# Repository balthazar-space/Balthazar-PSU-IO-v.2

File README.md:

# Balthazar

Open-hardware laptop computer modules description and concept.

These are electronic schematic modules as presented at https://balthazar.space/wiki/Balthazar with the main aim for team access. See the [main repository](https://github.com/balthazar-space/balthazar) for other designs.

# balthazar PSU/IO v.2

Module BalthazarPSU2 is a combined battery charger, buck-boost coverter, stereo power amplifier and usb 2.0 hub. A somehow revised version of BalthazarPSU module, this one has an added usb 2.0 hub based on Microchip USB2514B which was much more readily available in Europe than GL3520 chip.
We also work on USB 3.0 - due to the chip shortage/availability - we now have to wait.

KiCad 5.1.5 files.

## License

All resources except the keyboard firmware - which is licensed with with GPLv3 or later - licensed under the CERN Open Hardware Licence CERN-OHL W V.2.0

Version 2.0 of the CERN-OHL introduces three variants of the licence – strongly (S) reciprocal, weakly (W) reciprocal and permissive (P) – which aim to address specific constraints caused by different collaboration models currently used in open-hardware projects. 

The first two variants mean that if any product is made using an open hardware design, the design of that product, including any improvements or modifications, should be made available under the same licence as that of the original product. Permissive licences do not impose this condition.

See the [LICENSE.md](./LICENSE.md) file for more information.

## Funding

This project is funded through the [NGI Zero Entrust Fund](https://nlnet.nl/entrust), a fund
established by [NLnet](https://nlnet.nl) with financial support from the European Commission's
[Next Generation Internet](https://ngi.eu) program. Learn more on the [NLnet project page](https://nlnet.nl/project/Balthazar-Casing/).

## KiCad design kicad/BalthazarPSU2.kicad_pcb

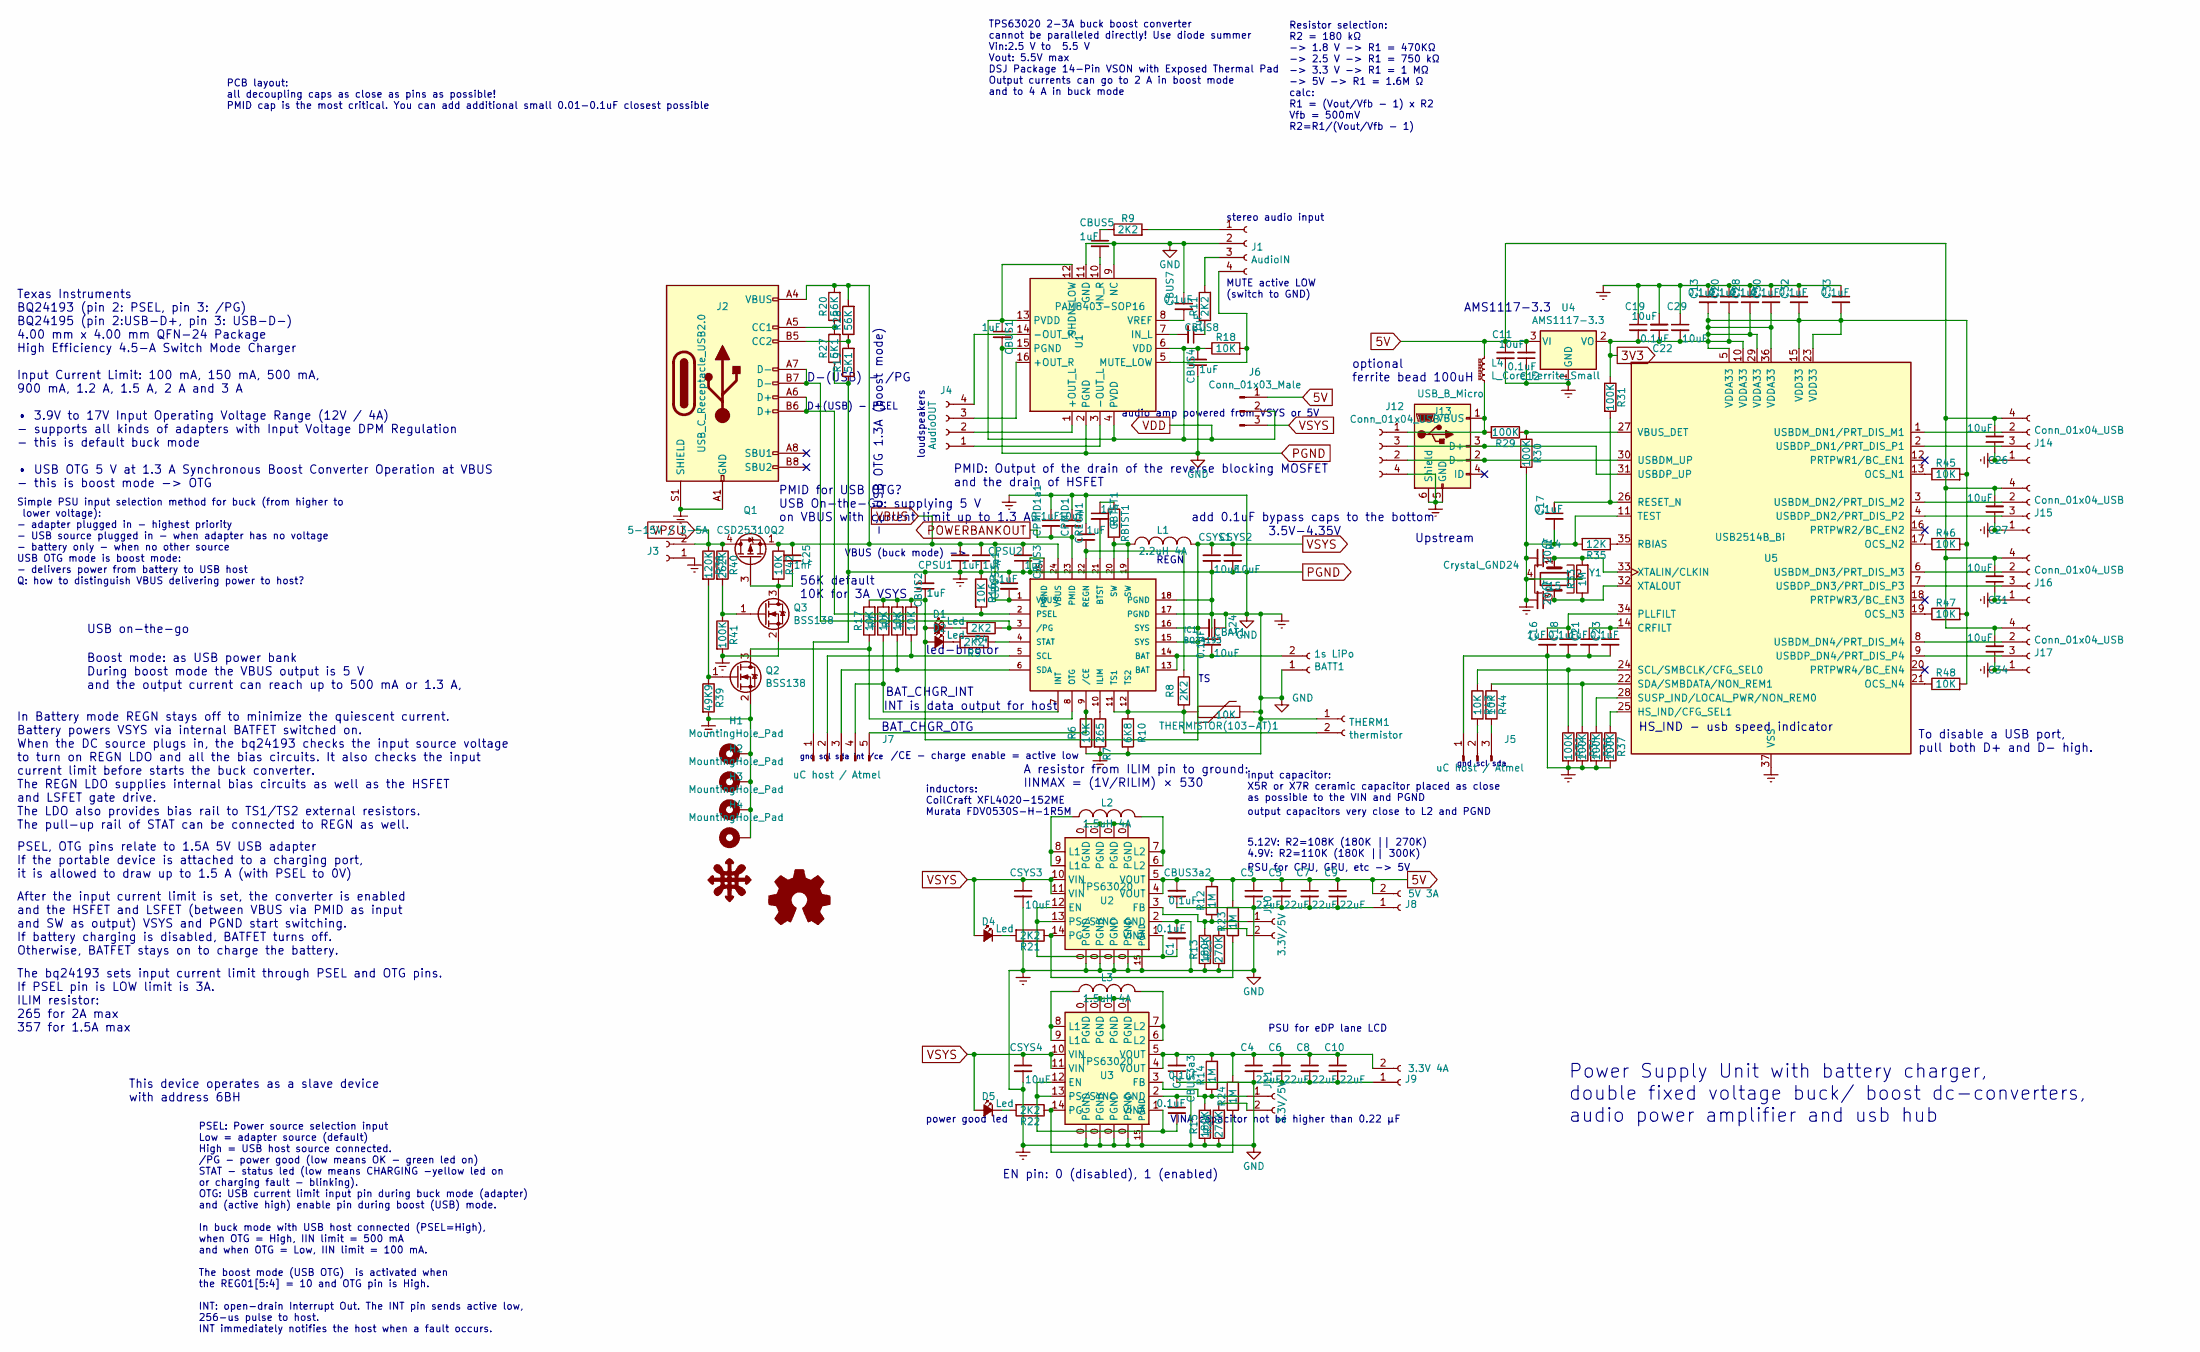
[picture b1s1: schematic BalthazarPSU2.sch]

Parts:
BATT1: 1s LiPo; TerminalBlock_bornier-2_P5.08mm
C1, C2, C11, C13, C17, C18, C19, C20, C23, C24, C28, C30, C32, C33: 0.1uF; C_1206_3216Metric
C3, C4, C5, C6, C7, C8, C9, C10: 22uF; C_1206_3216Metric
C12, C22, C26, C27, C29, C31, C34: 10uF; C_1206_3216Metric
C14, C15: 20pF; C_1206_3216Metric
C16, C21: 1uF; C_1206_3216Metric
C25: 1nF; C_0805_2012Metric
CBAT1: 10uF; C_1206_3216Metric
CBTST1: 1uF; C_1206_3216Metric
CBUS1, CBUS2, CBUS3, CBUS4, CBUS5, CBUS8: 1uF; C_1206_3216Metric
CBUS3a1, CBUS3a2, CBUS3a3: 0.1uF; C_0805_2012Metric
CBUS7: 0.1uF; C_1206_3216Metric
CPMID1: 10uF; C_1206_3216Metric
CPMID1a1: 0.1uF; C_0805_2012Metric
CPSU1, CPSU2: 1uF; C_1206_3216Metric
CREGN1: 1uF; C_1206_3216Metric
CSYS1, CSYS2, CSYS3, CSYS4: 10uF; C_1206_3216Metric
D1, D2, D4, D5: Led; LED_1206_3216Metric
H1, H2, H3, H4: MountingHole_Pad; MountingHole_2.2mm_M2_Pad
IC1: BQ24193; QFN-24-1EP_4x4mm_P0.5mm_EP2.7x2.7mm_ThermalVias
J1: AudioIN; PinSocket_1x04_P2.00mm_Vertical
J2: USB_C_Receptacle_USB2.0; USB_C_Receptacle_GCT_USB4085
J3: 5-15V / 3-5A; TerminalBlock_bornier-2_P5.08mm
J4: AudioOUT; PinSocket_1x04_P2.54mm_Vertical
J5: uC host / Atmel; PinSocket_1x03_P2.00mm_Vertical
J6: Conn_01x03_Male; PinHeader_1x03_P2.54mm_Vertical
J7: uC host / Atmel; PinSocket_1x05_P2.00mm_Vertical
J8: 5V 3A; TerminalBlock_bornier-2_P5.08mm
J9: 3.3V 4A; TerminalBlock_bornier-2_P5.08mm
J10, J11: 3.3V/5V; TestPoint_2Pads_Pitch2.54mm_Drill0.8mm
J12, J14, J15, J16, J17: Conn_01x04_USB; PinSocket_1x04_P2.00mm_Horizontal
J13: USB_B_Micro; USB_Micro-B_Molex-Balthazar
L1: 2.2uH 4A; L_Bourns_SRP7028A_7.3x6.6mm
L2, L3: 1.5uH 4A; L_Bourns_SRP7028A_7.3x6.6mm
L4: L_Core_Ferrite_Small; L_1206_3216Metric_Pad1.42x1.75mm_HandSolder
Q1: CSD25310Q2; Texas_DQK
Q2, Q3: BSS138; SOT-23
R1, R2, R3, R6, R16, R17, R42: 10K; R_0805_2012Metric_Pad1.15x1.40mm_HandSolder
R4, R5, R8, R9, R11, R21, R22: 2K2; R_1206_3216Metric
R7: 265; R_1206_3216Metric
R10: 6K8; R_1206_3216Metric
R12, R14, R23, R24: 1M; R_1206_3216Metric
R13, R15: 180K; R_1206_3216Metric
R18, R43, R44, R45, R46, R47, R48: 10K; R_1206_3216Metric
R19, R27: 5K1; R_0805_2012Metric_Pad1.15x1.40mm_HandSolder
R20, R28: 56K; R_0805_2012Metric_Pad1.15x1.40mm_HandSolder
R25, R26: 270K; R_1206_3216Metric
R29, R30, R31, R32, R34, R36, R37: 100K; R_1206_3216Metric
R33: 1M; R_0805_2012Metric
R35: 12K; R_1206_3216Metric
R38: 120K; R_1206_3216Metric
R39: 49K9; R_1206_3216Metric
R40: 262K; R_0805_2012Metric_Pad1.15x1.40mm_HandSolder
R41: 100K; R_0805_2012Metric_Pad1.15x1.40mm_HandSolder
RBTST1: R; R_1206_3216Metric
THERM1: thermistor; TestPoint_2Pads_Pitch2.54mm_Drill0.8mm
THERMISTOR(103-AT)1: 10K; R_1206_3216Metric
U1: PAM8403-SOP16; SOP-16_4.4x10.4mm_P1.27mm
U2, U3: TPS63020; WSON-14-1EP_4.0x4.0mm_P0.5mm_EP2.6x2.6mmThermalPads
U4: AMS1117-3.3; SOT-223-3_TabPin2
U5: USB2514B_Bi; QFN-36-1EP_6x6mm_P0.5mm_EP3.7x3.7mm
Y1: Crystal_GND24; Crystal_SMD_5032-4Pin_5.0x3.2mm

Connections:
3V3: C13.2, C19.2, C20.2, C22.1, C28.2, C29.2, C30.2, C32.2, C33.2, R31.1, R45.2, R46.2, R47.2, R48.2, U4.2 (VO), U5.5 (VDDA33), U5.10 (VDDA33), U5.15 (VDD33), U5.23 (VDD33), U5.29 (VDDA33), U5.36 (VDDA33)
5V: C3.1, C5.1, C7.1, C9.1, C11.1, C12.2, C26.2, C27.2, C31.2, C34.2, CBUS3a2.2, J6.1, J8.2, J14.4, J15.4, J16.4, J17.4, L4.2, R12.2, R23.2, U2.4 (VOUT), U2.5 (VOUT), U4.3 (VI)
unnamed: BATT1.2, CBAT1.2, IC1.13 (BAT), IC1.14 (BAT)
unnamed: C1.2, U2.1 (VINA), U2.12 (EN), U2.13 (PS/SYNC)
unnamed: C2.2, U3.1 (VINA), U3.12 (EN), U3.13 (PS/SYNC)
unnamed: C4.1, C6.1, C8.1, C10.1, CBUS3a3.2, J9.2, R14.2, R24.2, U3.4 (VOUT), U3.5 (VOUT)
unnamed: C14.1, R33.2, U5.33 (XTALIN/CLKIN), Y1.1
unnamed: C15.1, R33.1, U5.32 (XTALOUT), Y1.3
unnamed: C16.1, C18.1, U5.34 (PLLFILT)
unnamed: C17.1, R31.2, U5.26 (RESET_N)
unnamed: C21.1, C23.1, U5.14 (CRFILT)
unnamed: C25.1, Q1.3 (G), Q3.3 (D), R42.2
unnamed: CBTST1.1, RBTST1.1
unnamed: CBTST1.2, IC1.21 (BTST)
unnamed: CBUS5.1, R9.1
unnamed: CBUS5.2, U1.10 (IN_R)
unnamed: CBUS7.2, U1.8 (VREF)
unnamed: CBUS8.1, R11.1
unnamed: CBUS8.2, U1.7 (IN_L)
unnamed: CREGN1.2, IC1.22 (REGN), R8.1
unnamed: D1.2 (C), R4.2
unnamed: D2.2 (C), R5.2
unnamed: D4.2 (C), R21.2
unnamed: D5.2 (C), R22.2
unnamed: IC1.2 (PSEL), J2.A6 (D+), J2.B6 (D+), R16.2
unnamed: IC1.3 (/PG), J2.A7 (D-), J2.B7 (D-), R4.1
unnamed: IC1.4 (STAT), R5.1
unnamed: IC1.5 (SCL), J7.2, R3.1
unnamed: IC1.6 (SDA), J7.3, R2.1
unnamed: IC1.7 (INT), J7.4, R1.1
unnamed: IC1.8 (OTG), Q2.3 (D), R17.1
unnamed: IC1.9 (/CE), J7.5, R6.1
unnamed: IC1.10 (ILIM), R7.1
unnamed: IC1.11 (TS1), IC1.12 (TS2), R8.2, R10.1, THERM1.2, THERMISTOR(103-AT)1.2
unnamed: IC1.19 (SW), IC1.20 (SW), L1.1, RBTST1.2
unnamed: J1.1, R9.2
unnamed: J1.3, R11.2
unnamed: J1.4, R18.2, U1.5 (MUTE_LOW)
unnamed: J2.A5 (CC1), R20.1, R27.2
unnamed: J2.B5 (CC2), R19.2, R28.1
unnamed: J4.1, U1.3 (-OUT_L)
unnamed: J4.2, U1.1 (+OUT_L)
unnamed: J4.3, U1.16 (+OUT_R)
unnamed: J4.4, U1.14 (-OUT_R)
unnamed: J5.2, R43.2
unnamed: J5.3, R44.2
unnamed: J10.1, R12.1, R13.2, U2.3 (FB)
unnamed: J10.2, R25.2
unnamed: J11.1, R14.1, R15.2, U3.3 (FB)
unnamed: J11.2, R26.2
unnamed: J12.1, J13.1 (VBUS), L4.1, R29.2
unnamed: J12.2, J13.2 (D-), U5.30 (USBDM_UP)
unnamed: J12.3, J13.3 (D+), U5.31 (USBDP_UP)
unnamed: J14.2, U5.1 (USBDM_DN1/PRT_DIS_M1)
unnamed: J14.3, U5.2 (USBDP_DN1/PRT_DIS_P1)
unnamed: J15.2, U5.3 (USBDM_DN2/PRT_DIS_M2)
unnamed: J15.3, U5.4 (USBDP_DN2/PRT_DIS_P2)
unnamed: J16.2, U5.6 (USBDM_DN3/PRT_DIS_M3)
unnamed: J16.3, U5.7 (USBDP_DN3/PRT_DIS_P3)
unnamed: J17.2, U5.8 (USBDM_DN4/PRT_DIS_M4)
unnamed: J17.3, U5.9 (USBDP_DN4/PRT_DIS_P4)
unnamed: L2.1, U2.8 (L1), U2.9 (L1)
unnamed: L2.2, U2.6 (L2), U2.7 (L2)
unnamed: L3.1, U3.8 (L1), U3.9 (L1)
unnamed: L3.2, U3.6 (L2), U3.7 (L2)
unnamed: Q2.1 (G), R38.2, R39.1
unnamed: Q3.1 (G), R40.2, R41.1
unnamed: R21.1, R23.1, U2.14 (PG)
unnamed: R22.1, R24.1, U3.14 (PG)
unnamed: R29.1, R30.1, U5.27 (VBUS_DET)
unnamed: R32.1, R43.1, U5.24 (SCL/SMBCLK/CFG_SEL0)
unnamed: R34.1, R44.1, U5.22 (SDA/SMBDATA/NON_REM1)
unnamed: R35.1, U5.35 (RBIAS)
unnamed: R36.1, U5.28 (SUSP_IND/LOCAL_PWR/NON_REM0)
unnamed: R37.1, U5.25 (HS_IND/CFG_SEL1)
unnamed: R45.1, U5.13 (OCS_N1)
unnamed: R46.1, U5.17 (OCS_N2)
unnamed: R47.1, U5.19 (OCS_N3)
unnamed: R48.1, U5.21 (OCS_N4)
PGND: BATT1.1, C1.1, C2.1, C3.2, C4.2, C5.2, C6.2, C7.2, C8.2, C9.2, C10.2, C11.2, C12.1, C13.1, C14.2, C15.2, C16.2, C17.2, C18.2, C19.1, C20.1, C21.2, C22.2, C23.2, C24.1, C26.1, C27.1, C28.1, C29.1, C30.1, C31.1, C32.1, C33.1, C34.1, CBAT1.1, CBUS1.2, CBUS2.2, CBUS3.1, CBUS3a1.1, CBUS3a2.1, CBUS3a3.1, CBUS4.1, CBUS7.1, CPMID1.1, CPMID1a1.1, CPSU1.1, CPSU2.1, CREGN1.1, CSYS1.2, CSYS2.2, CSYS3.2, CSYS4.2, H1.1, H2.1, H3.1, H4.1, IC1.17 (PGND), IC1.18 (PGND), IC1.25 (PGND), J1.2, J2.A1 (GND), J2.A12 (GND), J2.B1 (GND), J2.B12 (GND), J2.S1 (SHIELD), J3.1, J5.1, J7.1, J8.1, J9.1, J12.4, J13.5 (GND), J13.6 (Shield), J14.1, J15.1, J16.1, J17.1, Q2.2 (S), Q3.2 (S), R6.2, R7.2, R10.2, R13.1, R15.1, R16.1, R19.1, R25.1, R26.1, R27.1, R30.2, R32.2, R34.2, R35.2, R36.2, R37.2, R39.2, R41.2, THERM1.1, THERMISTOR(103-AT)1.1, U1.2 (PGND), U1.9 (NC), U1.11 (GND), U1.15 (PGND), U2.0 (PGND), U2.2 (GND), U2.15 (PGND), U3.0 (PGND), U3.2 (GND), U3.15 (PGND), U4.1 (GND), U5.11 (TEST), U5.37 (VSS), Y1.2, Y1.4
POWERBANKOUT: CPMID1.2, CPMID1a1.2, IC1.23 (PMID)
VBUS: C25.2, CBUS3.2, CBUS3a1.2, CPSU1.2, CPSU2.2, IC1.1 (VBUS), IC1.24 (VBUS), J2.A4 (VBUS), J2.A9 (VBUS), J2.B4 (VBUS), J2.B9 (VBUS), Q1.1 (S), Q1.2 (S), Q1.5 (S), Q1.6 (S), Q1.8 (S), R20.2, R28.2, R42.1
VDD: CBUS1.1, CBUS4.2, J6.2, R18.1, U1.4 (PVDD), U1.6 (VDD), U1.12 (SHDN_LOW), U1.13 (PVDD)
VPSU: J3.2, Q1.4 (D), Q1.7 (D), R38.1, R40.1
VSYS: C24.2, CBUS2.1, CSYS1.1, CSYS2.1, CSYS3.1, CSYS4.1, D1.1 (A), D2.1 (A), D4.1 (A), D5.1 (A), IC1.15 (SYS), IC1.16 (SYS), J6.3, L1.2, R1.2, R2.2, R3.2, R17.2, U2.10 (VIN), U2.11 (VIN), U3.10 (VIN), U3.11 (VIN)

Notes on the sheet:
3.5V-4.35V
USB on-the-go
led-bicolor
BAT_CHGR_INT
BAT_CHGR_OTG
INT is data output for host
Texas Instruments BQ24193 (pin 2: PSEL, pin 3: /PG) BQ24195 (pin 2:USB-D+, pin 3: USB-D-) 4.00 mm x 4.00 mm QFN-24 Package High Efficiency 4.5-A Switch Mode Charger Input Current Limit: 100 mA, 150 mA, 500 mA, 900 mA, 1.2 A, 1.5 A, 2 A and 3 A • 3.9V to 17V Input Operating Voltage Range (12V / 4A) 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
PSEL, OTG pins relate to 1.5A 5V USB adapter If the portable device is attached to a charging port, it is allowed to draw up to 1.5 A (with PSEL to 0V)
In Battery mode REGN stays off to minimize the quiescent current. Battery powers VSYS via internal BATFET switched on. When the DC source plugs in, the bq24193 checks the input source voltage to turn on REGN LDO and all the bias circuits. It also checks the input current limit before starts the buc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
The bq24193 sets input current limit through PSEL and OTG pins. If PSEL pin is LOW limit is 3A. ILIM resistor: 265 for 2A max 357 for 1.5A max
After the input current limit is set, the converter is enabled and the HSFET and LSFET (between VBUS via PMID as input and SW as output) VSYS and PGND start switching. If battery charging is disabled, BATFET turns off. Otherwise, BATFET stays on to charge the battery.
PSU for CPU, GPU, etc -> 5V
TPS63020 2-3A buck boost converter cannot be paralleled directly! Use diode summer Vin:2.5 V to 5.5 V Vout: 5.5V max DSJ Package 14-Pin VSON with Exposed Thermal Pad Output currents can go to 2 A in boost mode and to 4 A in buck mode
inductors: CoilCraft XFL4020-152ME Murata FDV0530S-H-1R5M
Resistor selection: R2 = 180 kΩ -> 1.8 V -> R1 = 470KΩ -> 2.5 V -> R1 = 750 kΩ -> 3.3 V -> R1 = 1 MΩ -> 5V -> R1 = 1.6M Ω calc: R1 = (Vout/Vfb - 1) x R2 Vfb = 500mV R2=R1/(Vout/Vfb - 1)
REGN
stereo audio input
loudspeakers
MUTE active LOW (switch to GND)
D+(USB) - PSEL
Power Supply Unit with battery charger, double fixed voltage buck/ boost dc-converters, audio power amplifier and usb hub
PCB layout: all decoupling caps as close as pins as possible! PMID cap is the most critical. You can add additional small 0.01-0.1uF closest possible
PSU for eDP lane LCD
audio amp powered from VSYS or 5V
VBUS (buck mode) ->
Simple PSU input selection method for buck (from higher to lower voltage): - adapter plugged in - highest priority - USB source plugged in - when adapter has no voltage - battery only - when no other source USB OTG mode is boost mode: - delivers power from battery to USB host Q: how to distinguish 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
output capacitors very close to L2 and PGND
input capacitor: X5R or X7R ceramic capacitor placed as close as possible to the VIN and PGND
VINA capacitor not be higher than 0.22 μF
power good led
5.12V: R2=108K (180K || 270K) 4.9V: R2=110K (180K || 300K)
Boost mode: as USB power bank During boost mode the VBUS output is 5 V and the output current can reach up to 500 mA or 1.3 A,
gnd scl sda int /ce
add 0.1uF bypass caps to the bottom
EN pin: 0 (disabled), 1 (enabled)
/CE - charge enable = active low
56K default 10K for 3A
D-(USB) - /PG
HS_IND - usb speed indicator
Upstream

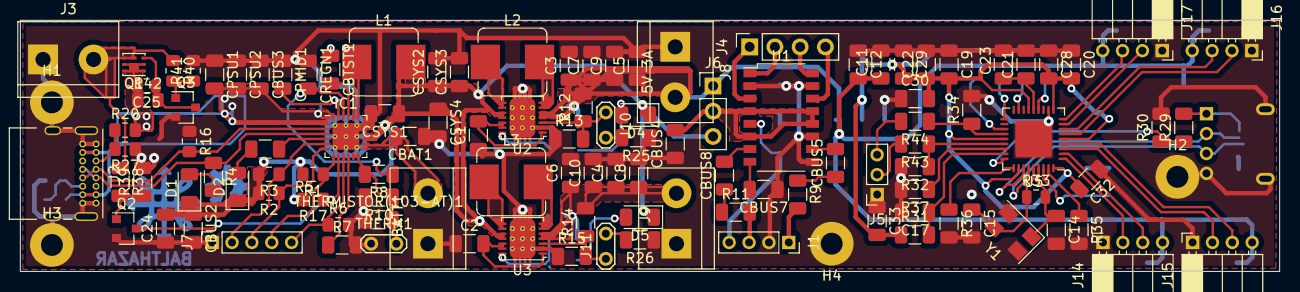
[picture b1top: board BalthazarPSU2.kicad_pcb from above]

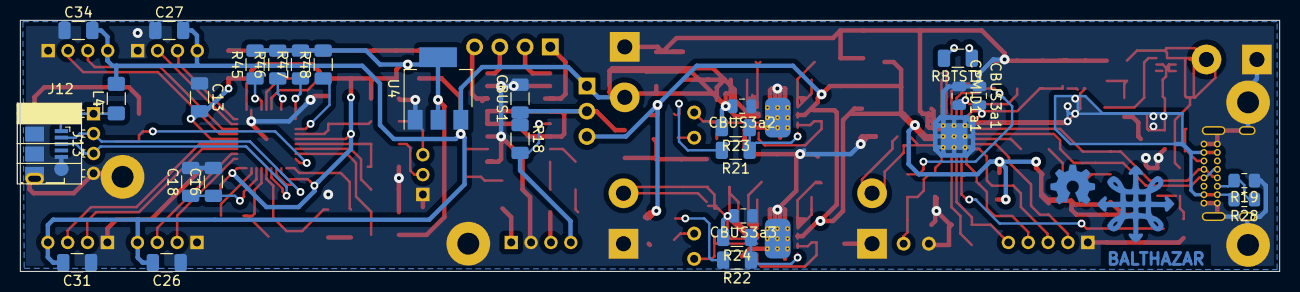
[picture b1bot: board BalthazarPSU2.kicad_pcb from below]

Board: 2 copper layers, 126.7 x 25.3 mm, 146 parts (28 on the bottom side), 85 nets.

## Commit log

2021-07-28 admin
